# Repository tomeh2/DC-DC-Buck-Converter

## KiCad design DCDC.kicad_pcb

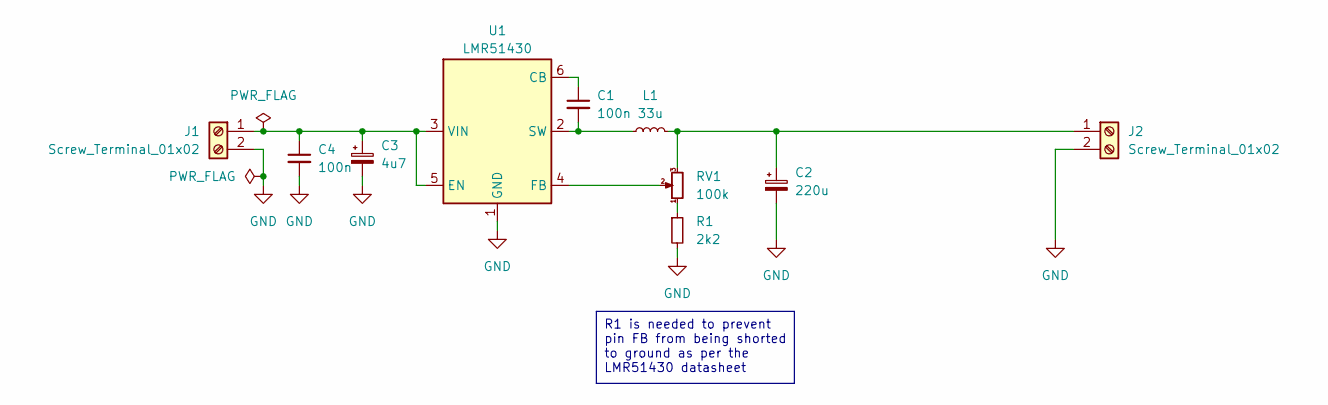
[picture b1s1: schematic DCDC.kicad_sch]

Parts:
C1, C4: 100n; C_0805_2012Metric_Pad1.18x1.45mm_HandSolder; Mouser Part Number 810-C2012X7R1H104K-2
C2: 220u; CP_Elec_10x10.5; Mouser Part Number 667-EEE-FP1H221AP
C3: 4u7; C_0805_2012Metric_Pad1.18x1.45mm_HandSolder; Mouser Part Number 810-C2012X7R475K125C
J1, J2: Screw_Terminal_01x02; 282834-2_1; Mouser Part Number 571-282834-2
L1: 33u; L_Bourns_SRP1038C_10.0x10.0mm; Mouser Part Number 652-SRP1050WA-330M
R1: 2k2; R_0805_2012Metric_Pad1.20x1.40mm_HandSolder; Mouser Part Number 603-RC0805FR-132K2L
RV1: 100k; PV37W104C01B00; Mouser Part Number 81-PV37W104C01B00
U1: LMR51430; SOT-23-6; Mouser Part Number 595-LMR51430YFDDCR

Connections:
GND: C2.2, C3.2, C4.2, J1.2, J2.2, R1.2, U1.1 (GND)
unnamed: C3.1, C4.1, J1.1, U1.3 (VIN), U1.5 (EN)
unnamed: C2.1, J2.1, L1.2, RV1.3
unnamed: R1.1, RV1.1
unnamed: C1.1, U1.6 (CB)
unnamed: RV1.2, U1.4 (FB)
unnamed: C1.2, L1.1, U1.2 (SW)

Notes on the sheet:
R1 is needed to prevent pin FB from being shorted to ground as per the LMR51430 datasheet

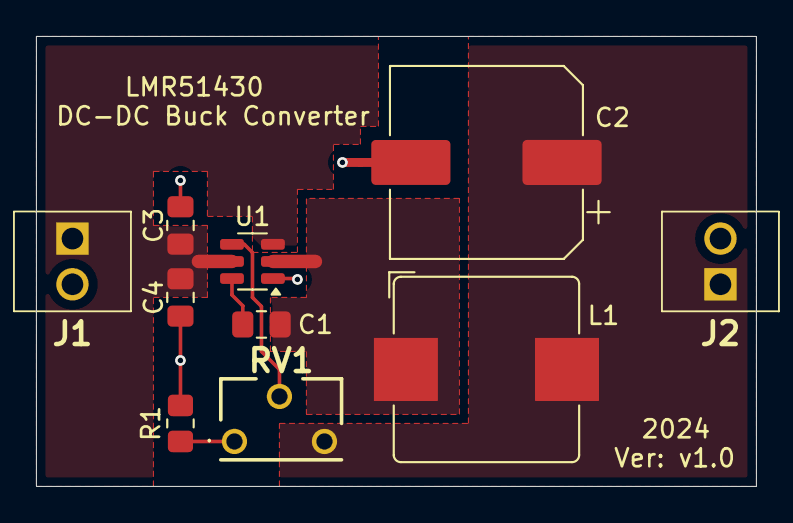
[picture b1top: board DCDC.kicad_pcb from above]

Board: 2 copper layers, 40.0 x 25.0 mm, 10 parts (0 on the bottom side), 7 nets.

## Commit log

2024-09-01 First commit of a finished project
